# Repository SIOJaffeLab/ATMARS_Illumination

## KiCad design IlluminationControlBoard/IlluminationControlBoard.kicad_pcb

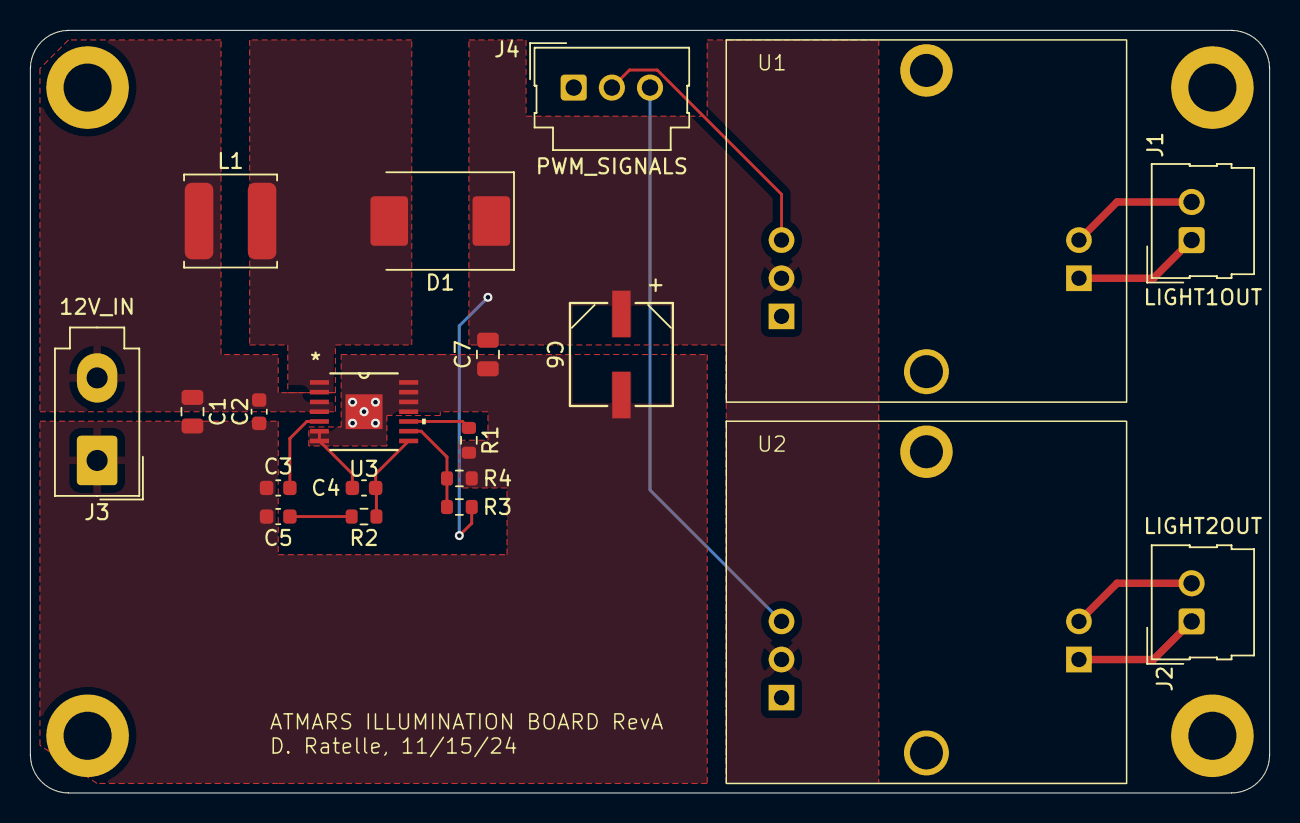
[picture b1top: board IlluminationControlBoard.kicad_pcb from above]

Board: 2 copper layers, 82.6 x 50.8 mm, 20 parts (0 on the bottom side), 15 nets.

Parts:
C1: 10uF, 25V; C_0805_2012Metric
C2: 100nF, 25V; C_0603_1608Metric
C3: 47nF; C_0603_1608Metric
C4: 1.5nF; C_0603_1608Metric
C5: 15nF; C_0603_1608Metric
C6: 27uF; CAP_PC_6P3X8_NCH
C7: 1uF, 35V; C_0805_2012Metric
D1: 550mV, 5A; D_SMC
J1: LIGHT1OUT; Molex_SL_171971-0002_1x02_P2.54mm_Vertical
J2: LIGHT2OUT; Molex_SL_171971-0002_1x02_P2.54mm_Vertical
J3: 12V_IN; Molex_Mini-Fit_Jr_5566-02A_2x01_P4.20mm_Vertical
J4: PWM_SIGNALS; Molex_SL_171971-0003_1x03_P2.54mm_Vertical
L1: 3.3uH; L_TDK_VLS6045EX_VLS6045AF
R1: 60.4k; R_0603_1608Metric
R2: 2k; R_0603_1608Metric
R3: 113k; R_0603_1608Metric
R4: 10k; R_0603_1608Metric
U1, U2: DWE_DRIVER
U3: TPS55340PWPR; PWP14

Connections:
12V: C1.1, C2.1, J3.2, L1.1, U3.3 (VIN), U3.4 (EN)
15V: C6.1, C7.2, D1.1 (K), R3.2, U1.2 (VIN), U2.2 (VIN)
GND: C1.2, C2.2, C3.1, C4.2, C5.2, C6.2, C7.1, J3.1, J4.1, R1.2, R4.1, U1.1 (GND), U2.1 (GND), U3.6 (SYNC), U3.7 (AGND), U3.11 (NC), U3.12 (PGND), U3.13 (PGND), U3.14 (PGND), U3.15 (EPAD)
L1_MINUS: J1.1, U1.5 (LED-)
L1_PLUS: J1.2, U1.4 (LED+)
L1_PWM: J4.2, U1.3 (PWM)
L2_MINUS: J2.1, U2.5 (LED-)
L2_PLUS: J2.2, U2.4 (LED+)
L2_PWM: J4.3, U2.3 (PWM)
unnamed: C5.1, R2.2
unnamed: D1.2 (A), L1.2, U3.1 (SW), U3.2 (SW)
unnamed: C4.1, R2.1, U3.8 (COMP)
unnamed: R3.1, R4.2, U3.9 (FB)
unnamed: R1.1, U3.10 (FREQ)
unnamed: C3.2, U3.5 (SS)

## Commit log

2024-11-13 Initial schematic
2024-11-13 DWE custom symbol/footprint made
2024-11-14 Schematic updates
2024-11-15 Schematic Update
    Added 15V regulator for LED maximum brightness
2024-11-15 SchematicUpdates
2024-11-16 PCB designed
    Designed and populated PCB to provide 15V to illumination.
2024-11-18 Added gitignore from VOLT PCB
2024-11-19 Applied gitignore to old files through CLI
2024-11-26 FabFiles
